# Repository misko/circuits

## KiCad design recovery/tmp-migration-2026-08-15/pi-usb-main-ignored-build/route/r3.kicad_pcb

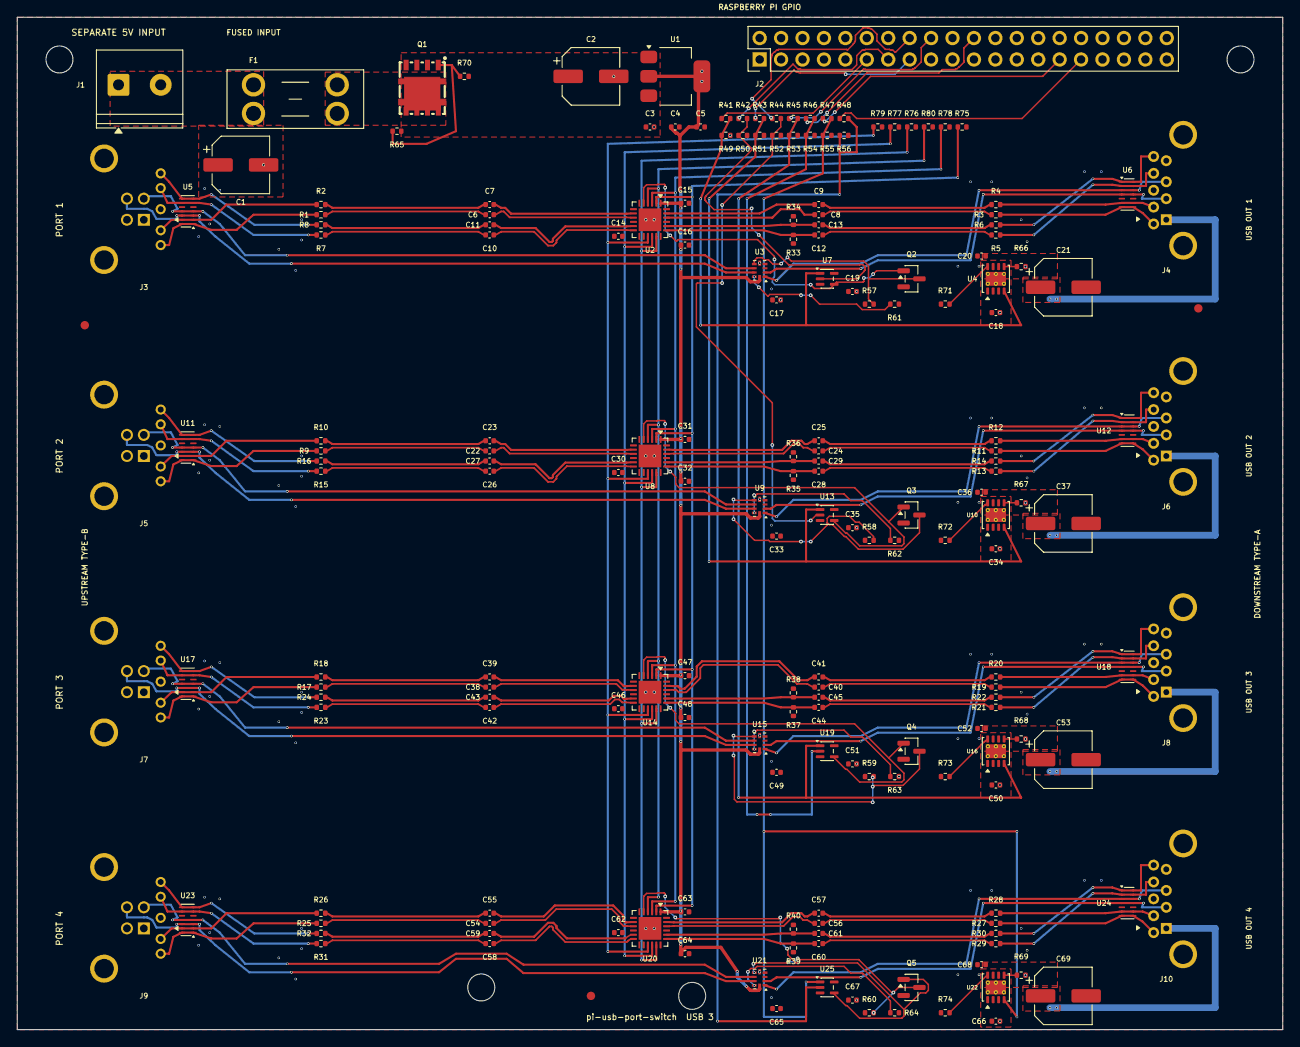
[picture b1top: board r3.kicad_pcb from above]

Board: 4 copper layers, 150.0 x 120.0 mm, 197 parts (0 on the bottom side), 164 nets.

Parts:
C1, C2: 180uF; CP_Elec_6.3x5.8
C3, C6, C7, C8, C9, C10, C11, C14, C15, C17, C18, C19, C20, C22, C23, C24, C25, C26, C27, C30, C31, C33, C34, C35, C36, C38, C39, C40, C41, C42, C43, C46, C47, C49, C50, C51, C52, C54, C55, C56, C57, C58, C59, C62, C63, C65, C66, C67, C68: 100nF; C_0402_1005Metric
C4: 1uF; C_0402_1005Metric
C5, C16, C32, C48, C64: 10uF; C_0402_1005Metric
C12, C13, C28, C29, C44, C45, C60, C61: 330nF; C_0402_1005Metric
C21, C37, C53, C69: 150uF; CP_Elec_6.3x5.8
F1: C5249699; Keystone_3568_Mini_Blade_Fuse_Holder
FID1, FID2, FID3: Fiducial_1mm_Mask2mm
H1, H2, H3, H4: MountingHole_3.2mm_M3
J1: C3819953; Phoenix_1935161_PT_1p5_2_5p0_H
J2: C5364405; PinHeader_2x20_P2.54mm_Vertical
J3, J5, J7, J9: C5334230; Wurth_692221030100_USB3_B
J4, J6, J8, J10: 692121030100; Wurth_692121030100_USB3_A
Q1: C397981; PowerDI5060-8
Q2, Q3, Q4, Q5: C85049; SOT-23
R1, R2, R3, R4, R5, R6, R7, R8, R9, R10, R11, R12, R13, R14, R15, R16, R17, R18, R19, R20, R21, R22, R23, R24, R25, R26, R27, R28, R29, R30, R31, R32: 2.2Ω; R_0402_1005Metric
R33, R34, R35, R36, R37, R38, R39, R40: 220kΩ; R_0402_1005Metric
R41, R42, R43, R44, R45, R46, R47, R48: 1kΩ; R_0402_1005Metric
R49, R50, R51, R52, R53, R54, R55, R56, R57, R58, R59, R60, R61, R62, R63, R64, R65, R66, R67, R68, R69: 100kΩ; R_0402_1005Metric
R70: 1MΩ; R_0402_1005Metric
R71, R72, R73, R74: 10kΩ; R_0402_1005Metric
R75, R76, R77, R78, R79, R80: 4.7kΩ; R_0402_1005Metric
U1: C7527500; SOT-223-3_TabPin2
U2, U8, U14, U20: C2675181; TUSB522P_RGE24_4x4_P0.5
U3, U9, U15, U21: C129313; TS3USB221E_RSE10_2x1.5_P0.4
U4, U10, U16, U22: C130056; VSON-8-1EP_3x3mm_P0.65mm_EP1.65x2.4mm_ThermalVias
U5, U6, U11, U12, U17, U18, U23, U24: C962978; TPD6E05U06_RVZ14_3.5x1.35_P0.5
U7, U13, U19, U25: C7832; SC-70-5

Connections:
3V3: C4.1, C5.1, C14.1, C15.1, C16.1, C17.1, C19.1, C30.1, C31.1, C32.1, C33.1, C35.1, C46.1, C47.1, C48.1, C49.1, C51.1, C62.1, C63.1, C64.1, C65.1, C67.1, R57.1, R58.1, R59.1, R60.1, R71.1, R72.1, R73.1, R74.1, U1.2, U2.1, U2.13, U3.10, U7.5, U8.1, U8.13, U9.10, U13.5, U14.1, U14.13, U15.10, U19.5, U20.1, U20.13, U21.10, U25.5
DATA_EN1: R42.2, R50.1, U7.2
DATA_EN2: R44.2, R52.1, U13.2
DATA_EN3: R46.2, R54.1, U19.2
DATA_EN4: R48.2, R56.1, U25.2
DATA_OK1: Q2.1, U2.5, U7.4
DATA_OK2: Q3.1, U8.5, U13.4
DATA_OK3: Q4.1, U14.5, U19.4
DATA_OK4: Q5.1, U20.5, U25.4
EXT_5V_FUSED: F1.2, Q1.5, Q1.6, Q1.7, Q1.8
EXT_5V_RAW: C1.1, F1.1, J1.1
GND: C1.2, C2.2, C3.2, C4.2, C5.2, C14.2, C15.2, C16.2, C17.2, C18.2, C19.2, C20.2, C21.2, C30.2, C31.2, C32.2, C33.2, C34.2, C35.2, C36.2, C37.2, C46.2, C47.2, C48.2, C49.2, C50.2, C51.2, C52.2, C53.2, C62.2, C63.2, C64.2, C65.2, C66.2, C67.2, C68.2, C69.2, J1.2, J2.6, J2.9, J2.14, J2.20, J2.25, J2.30, J2.34, J2.39, J3.4, J3.7, J3.10, J4.4, J4.7, J4.10, J5.4, J5.7, J5.10, J6.4, J6.7, J6.10, J7.4, J7.7, J7.10, J8.4, J8.7, J8.10, J9.4, J9.7, J9.10, J10.4, J10.7, J10.10, Q2.2, Q3.2, Q4.2, Q5.2, R33.2, R34.2, R35.2, R36.2, R37.2, R38.2, R39.2, R40.2, R49.2, R50.2, R51.2, R52.2, R53.2, R54.2, R55.2, R56.2, R61.2, R62.2, R63.2, R64.2, R65.2, R66.2, R67.2, R68.2, R69.2, R75.2, R76.2, R77.2, R78.2, R79.2, R80.2, U1.1, U2.10, U2.21, U2.25, U3.5, U4.1, U4.9, U5.5, U5.10, U6.5, U6.10, U7.3, U8.10, U8.21, U8.25, U9.5, U10.1, U10.9, U11.5, U11.10, U12.5, U12.10, U13.3, U14.10, U14.21, U14.25, U15.5, U16.1, U16.9, U17.5, U17.10, U18.5, U18.10, U19.3, U20.10, U20.21, U20.25, U21.5, U22.1, U22.9, U23.5, U23.10, U24.5, U24.10, U25.3
GPIO5_RAW: J2.29, R47.1
GPIO6_RAW: J2.31, R48.1
GPIO17_RAW: J2.11, R41.1
GPIO22_RAW: J2.15, R43.1
GPIO23_RAW: J2.16, R44.1
GPIO24_RAW: J2.18, R45.1
GPIO25_RAW: J2.22, R46.1
GPIO27_RAW: J2.13, R42.1
ILIM1: R66.1, U4.5
ILIM2: R67.1, U10.5
ILIM3: R68.1, U16.5
ILIM4: R69.1, U22.5
P5V_PROTECTED: C2.1, C3.1, C18.1, C34.1, C50.1, C66.1, Q1.2, Q1.3, Q1.4, R70.1, U1.3, U4.2, U4.3, U10.2, U10.3, U16.2, U16.3, U22.2, U22.3
PWR_EN1: R41.2, R49.1, U4.4, U7.1
PWR_EN2: R43.2, R51.1, U10.4, U13.1
PWR_EN3: R45.2, R53.1, U16.4, U19.1
PWR_EN4: R47.2, R55.1, U22.4, U25.1
RPP_GATE: Q1.1, R65.1, R70.2
TUSB_DE1: R77.1, U2.16, U8.16, U14.16, U20.16
TUSB_DE2: R78.1, U2.3, U8.3, U14.3, U20.3
TUSB_EQ1: R75.1, U2.2, U8.2, U14.2, U20.2
TUSB_EQ2: R76.1, U2.17, U8.17, U14.17, U20.17
TUSB_OS1: R79.1, U2.15, U8.15, U14.15, U20.15
TUSB_OS2: R80.1, U2.4, U8.4, U14.4, U20.4
USB1_HS_DN_N: J4.2, U3.2, U6.4, U6.11
USB1_HS_DN_P: J4.3, U3.1, U6.3, U6.12
USB1_HS_UP_N: J3.2, U3.7, U5.4, U5.11
USB1_HS_UP_P: J3.3, U3.8, U5.3, U5.12
USB1_SS_RX_DN_CONN_N: J4.5, R6.1, U6.1, U6.14
USB1_SS_RX_DN_CONN_P: J4.6, R5.1, U6.2, U6.13
USB1_SS_RX_DN_IC_N: C13.2, R34.1, U2.20
USB1_SS_RX_DN_IC_P: C12.2, R33.1, U2.19
USB1_SS_RX_DN_MID_N: C13.1, R6.2
USB1_SS_RX_DN_MID_P: C12.1, R5.2
USB1_SS_RX_UP_CONN_N: J3.5, R8.1, U5.7, U5.8
USB1_SS_RX_UP_CONN_P: J3.6, R7.1, U5.6, U5.9
USB1_SS_RX_UP_IC_N: C11.1, U2.11
USB1_SS_RX_UP_IC_P: C10.1, U2.12
USB1_SS_RX_UP_MID_N: C11.2, R8.2
USB1_SS_RX_UP_MID_P: C10.2, R7.2
USB1_SS_TX_DN_CONN_N: J4.8, R4.1, U6.6, U6.9
USB1_SS_TX_DN_CONN_P: J4.9, R3.1, U6.7, U6.8
USB1_SS_TX_DN_IC_N: C9.1, U2.23
USB1_SS_TX_DN_IC_P: C8.1, U2.22
USB1_SS_TX_DN_MID_N: C9.2, R4.2
USB1_SS_TX_DN_MID_P: C8.2, R3.2
USB1_SS_TX_UP_CONN_N: J3.8, R2.1, U5.2, U5.13
USB1_SS_TX_UP_CONN_P: J3.9, R1.1, U5.1, U5.14
USB1_SS_TX_UP_IC_N: C7.2, U2.8
USB1_SS_TX_UP_IC_P: C6.2, U2.9
USB1_SS_TX_UP_MID_N: C7.1, R2.2
USB1_SS_TX_UP_MID_P: C6.1, R1.2
USB2_HS_DN_N: J6.2, U9.2, U12.4, U12.11
USB2_HS_DN_P: J6.3, U9.1, U12.3, U12.12
USB2_HS_UP_N: J5.2, U9.7, U11.4, U11.11
USB2_HS_UP_P: J5.3, U9.8, U11.3, U11.12
USB2_OE1: Q2.3, R57.2, U3.6
USB2_OE2: Q3.3, R58.2, U9.6
USB2_OE3: Q4.3, R59.2, U15.6
USB2_OE4: Q5.3, R60.2, U21.6
USB2_SEL1: R61.1, U3.9
USB2_SEL2: R62.1, U9.9
USB2_SEL3: R63.1, U15.9
USB2_SEL4: R64.1, U21.9
USB2_SS_RX_DN_CONN_N: J6.5, R14.1, U12.1, U12.14
USB2_SS_RX_DN_CONN_P: J6.6, R13.1, U12.2, U12.13
USB2_SS_RX_DN_IC_N: C29.2, R36.1, U8.20
USB2_SS_RX_DN_IC_P: C28.2, R35.1, U8.19
USB2_SS_RX_DN_MID_N: C29.1, R14.2
USB2_SS_RX_DN_MID_P: C28.1, R13.2
USB2_SS_RX_UP_CONN_N: J5.5, R16.1, U11.7, U11.8
USB2_SS_RX_UP_CONN_P: J5.6, R15.1, U11.6, U11.9
USB2_SS_RX_UP_IC_N: C27.1, U8.11
USB2_SS_RX_UP_IC_P: C26.1, U8.12
USB2_SS_RX_UP_MID_N: C27.2, R16.2
USB2_SS_RX_UP_MID_P: C26.2, R15.2
USB2_SS_TX_DN_CONN_N: J6.8, R12.1, U12.6, U12.9
USB2_SS_TX_DN_CONN_P: J6.9, R11.1, U12.7, U12.8
USB2_SS_TX_DN_IC_N: C25.1, U8.23
USB2_SS_TX_DN_IC_P: C24.1, U8.22
USB2_SS_TX_DN_MID_N: C25.2, R12.2
USB2_SS_TX_DN_MID_P: C24.2, R11.2
USB2_SS_TX_UP_CONN_N: J5.8, R10.1, U11.2, U11.13
USB2_SS_TX_UP_CONN_P: J5.9, R9.1, U11.1, U11.14
USB2_SS_TX_UP_IC_N: C23.2, U8.8
USB2_SS_TX_UP_IC_P: C22.2, U8.9
USB2_SS_TX_UP_MID_N: C23.1, R10.2
USB2_SS_TX_UP_MID_P: C22.1, R9.2
USB3_HS_DN_N: J8.2, U15.2, U18.4, U18.11
USB3_HS_DN_P: J8.3, U15.1, U18.3, U18.12
USB3_HS_UP_N: J7.2, U15.7, U17.4, U17.11
USB3_HS_UP_P: J7.3, U15.8, U17.3, U17.12
USB3_SS_RX_DN_CONN_N: J8.5, R22.1, U18.1, U18.14
USB3_SS_RX_DN_CONN_P: J8.6, R21.1, U18.2, U18.13
USB3_SS_RX_DN_IC_N: C45.2, R38.1, U14.20
USB3_SS_RX_DN_IC_P: C44.2, R37.1, U14.19
USB3_SS_RX_DN_MID_N: C45.1, R22.2
USB3_SS_RX_DN_MID_P: C44.1, R21.2
USB3_SS_RX_UP_CONN_N: J7.5, R24.1, U17.7, U17.8
USB3_SS_RX_UP_CONN_P: J7.6, R23.1, U17.6, U17.9
USB3_SS_RX_UP_IC_N: C43.1, U14.11
USB3_SS_RX_UP_IC_P: C42.1, U14.12
USB3_SS_RX_UP_MID_N: C43.2, R24.2
USB3_SS_RX_UP_MID_P: C42.2, R23.2
USB3_SS_TX_DN_CONN_N: J8.8, R20.1, U18.6, U18.9
USB3_SS_TX_DN_CONN_P: J8.9, R19.1, U18.7, U18.8
USB3_SS_TX_DN_IC_N: C41.1, U14.23
USB3_SS_TX_DN_IC_P: C40.1, U14.22
USB3_SS_TX_DN_MID_N: C41.2, R20.2
USB3_SS_TX_DN_MID_P: C40.2, R19.2
USB3_SS_TX_UP_CONN_N: J7.8, R18.1, U17.2, U17.13
USB3_SS_TX_UP_CONN_P: J7.9, R17.1, U17.1, U17.14
USB3_SS_TX_UP_IC_N: C39.2, U14.8
USB3_SS_TX_UP_IC_P: C38.2, U14.9
USB3_SS_TX_UP_MID_N: C39.1, R18.2
USB3_SS_TX_UP_MID_P: C38.1, R17.2
USB4_HS_DN_N: J10.2, U21.2, U24.4, U24.11
USB4_HS_DN_P: J10.3, U21.1, U24.3, U24.12
USB4_HS_UP_N: J9.2, U21.7, U23.4, U23.11
USB4_HS_UP_P: J9.3, U21.8, U23.3, U23.12
USB4_SS_RX_DN_CONN_N: J10.5, R30.1, U24.1, U24.14
USB4_SS_RX_DN_CONN_P: J10.6, R29.1, U24.2, U24.13
USB4_SS_RX_DN_IC_N: C61.2, R40.1, U20.20
USB4_SS_RX_DN_IC_P: C60.2, R39.1, U20.19
USB4_SS_RX_DN_MID_N: C61.1, R30.2
USB4_SS_RX_DN_MID_P: C60.1, R29.2
USB4_SS_RX_UP_CONN_N: J9.5, R32.1, U23.7, U23.8
USB4_SS_RX_UP_CONN_P: J9.6, R31.1, U23.6, U23.9
USB4_SS_RX_UP_IC_N: C59.1, U20.11
USB4_SS_RX_UP_IC_P: C58.1, U20.12
USB4_SS_RX_UP_MID_N: C59.2, R32.2
USB4_SS_RX_UP_MID_P: C58.2, R31.2
USB4_SS_TX_DN_CONN_N: J10.8, R28.1, U24.6, U24.9
USB4_SS_TX_DN_CONN_P: J10.9, R27.1, U24.7, U24.8
USB4_SS_TX_DN_IC_N: C57.1, U20.23
USB4_SS_TX_DN_IC_P: C56.1, U20.22
USB4_SS_TX_DN_MID_N: C57.2, R28.2
USB4_SS_TX_DN_MID_P: C56.2, R27.2
USB4_SS_TX_UP_CONN_N: J9.8, R26.1, U23.2, U23.13
USB4_SS_TX_UP_CONN_P: J9.9, R25.1, U23.1, U23.14
USB4_SS_TX_UP_IC_N: C55.2, U20.8
USB4_SS_TX_UP_IC_P: C54.2, U20.9
USB4_SS_TX_UP_MID_N: C55.1, R26.2
USB4_SS_TX_UP_MID_P: C54.1, R25.2
VBUS1_SW: C20.1, C21.1, J4.1, U4.6, U4.7
VBUS2_SW: C36.1, C37.1, J6.1, U10.6, U10.7
VBUS3_SW: C52.1, C53.1, J8.1, U16.6, U16.7
VBUS4_SW: C68.1, C69.1, J10.1, U22.6, U22.7
VBUS_FAULT1_N: R71.2, U4.8
VBUS_FAULT2_N: R72.2, U10.8
VBUS_FAULT3_N: R73.2, U16.8
VBUS_FAULT4_N: R74.2, U22.8
